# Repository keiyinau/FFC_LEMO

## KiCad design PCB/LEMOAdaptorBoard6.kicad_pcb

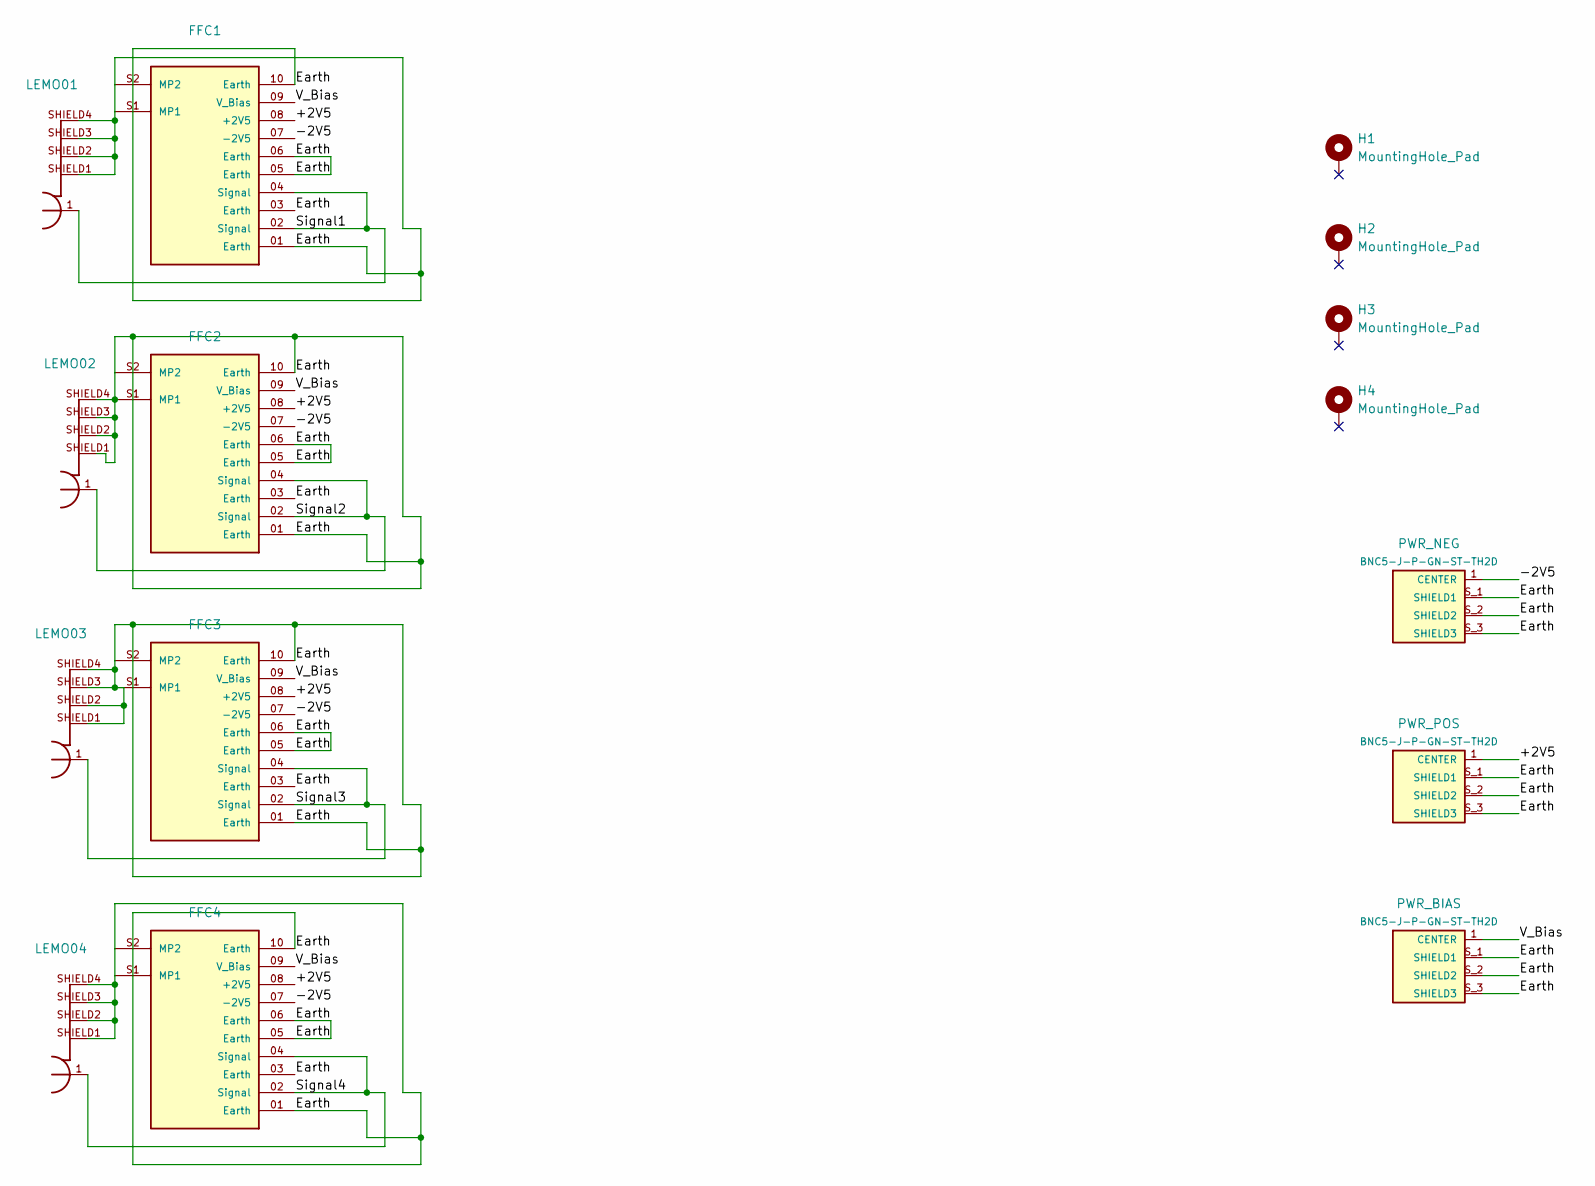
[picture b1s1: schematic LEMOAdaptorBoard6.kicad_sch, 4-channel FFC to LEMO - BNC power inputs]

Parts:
FFC1: FFC_Connector_Vertical; FFC1
FFC2: FFC_Connector_Vertical; FFC2
FFC3: FFC_Connector_Vertical; FFC3
FFC4: FFC_Connector_Vertical; FFC4
H1: MountingHole_Pad; H1
H2: MountingHole_Pad; H2
H3: MountingHole_Pad; H3
H4: MountingHole_Pad; H4
LEMO01: FPL.00.250.NTD; LEMO01
LEMO02: FPL.00.250.NTD; LEMO02
LEMO03: FPL.00.250.NTD; LEMO03
LEMO04: FPL.00.250.NTD; LEMO04
PWR_BIAS: BNC5-J-P-GN-ST-TH2D; PWR_BIAS
PWR_NEG: BNC5-J-P-GN-ST-TH2D; PWR_NEG
PWR_POS: BNC5-J-P-GN-ST-TH2D; PWR_POS

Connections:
/+2V5: FFC1.08 (+2V5), FFC2.08 (+2V5), FFC3.08 (+2V5), FFC4.08 (+2V5), PWR_POS.1 (CENTER)
/-2V5: FFC1.07 (-2V5), FFC2.07 (-2V5), FFC3.07 (-2V5), FFC4.07 (-2V5), PWR_NEG.1 (CENTER)
/Earth: FFC1.01 (Earth), FFC1.03 (Earth), FFC1.05 (Earth), FFC1.06 (Earth), FFC1.10 (Earth), FFC1.S1 (MP1), FFC1.S2 (MP2), FFC2.01 (Earth), FFC2.03 (Earth), FFC2.05 (Earth), FFC2.06 (Earth), FFC2.10 (Earth), FFC2.S1 (MP1), FFC2.S2 (MP2), FFC3.01 (Earth), FFC3.03 (Earth), FFC3.05 (Earth), FFC3.06 (Earth), FFC3.10 (Earth), FFC3.S1 (MP1), FFC3.S2 (MP2), FFC4.01 (Earth), FFC4.03 (Earth), FFC4.05 (Earth), FFC4.06 (Earth), FFC4.10 (Earth), FFC4.S1 (MP1), FFC4.S2 (MP2), LEMO01.SHIELD1, LEMO01.SHIELD2, LEMO01.SHIELD3, LEMO01.SHIELD4, LEMO02.SHIELD1, LEMO02.SHIELD2, LEMO02.SHIELD3, LEMO02.SHIELD4, LEMO03.SHIELD1, LEMO03.SHIELD2, LEMO03.SHIELD3, LEMO03.SHIELD4, LEMO04.SHIELD1, LEMO04.SHIELD2, LEMO04.SHIELD3, LEMO04.SHIELD4, PWR_BIAS.S_1 (SHIELD1), PWR_BIAS.S_2 (SHIELD2), PWR_BIAS.S_3 (SHIELD3), PWR_NEG.S_1 (SHIELD1), PWR_NEG.S_2 (SHIELD2), PWR_NEG.S_3 (SHIELD3), PWR_POS.S_1 (SHIELD1), PWR_POS.S_2 (SHIELD2), PWR_POS.S_3 (SHIELD3)
/Signal1: FFC1.02 (Signal), FFC1.04 (Signal), LEMO01.1
/Signal2: FFC2.02 (Signal), FFC2.04 (Signal), LEMO02.1
/Signal3: FFC3.02 (Signal), FFC3.04 (Signal), LEMO03.1
/Signal4: FFC4.02 (Signal), FFC4.04 (Signal), LEMO04.1
/V_Bias: FFC1.09 (V_Bias), FFC2.09 (V_Bias), FFC3.09 (V_Bias), FFC4.09 (V_Bias), PWR_BIAS.1 (CENTER)

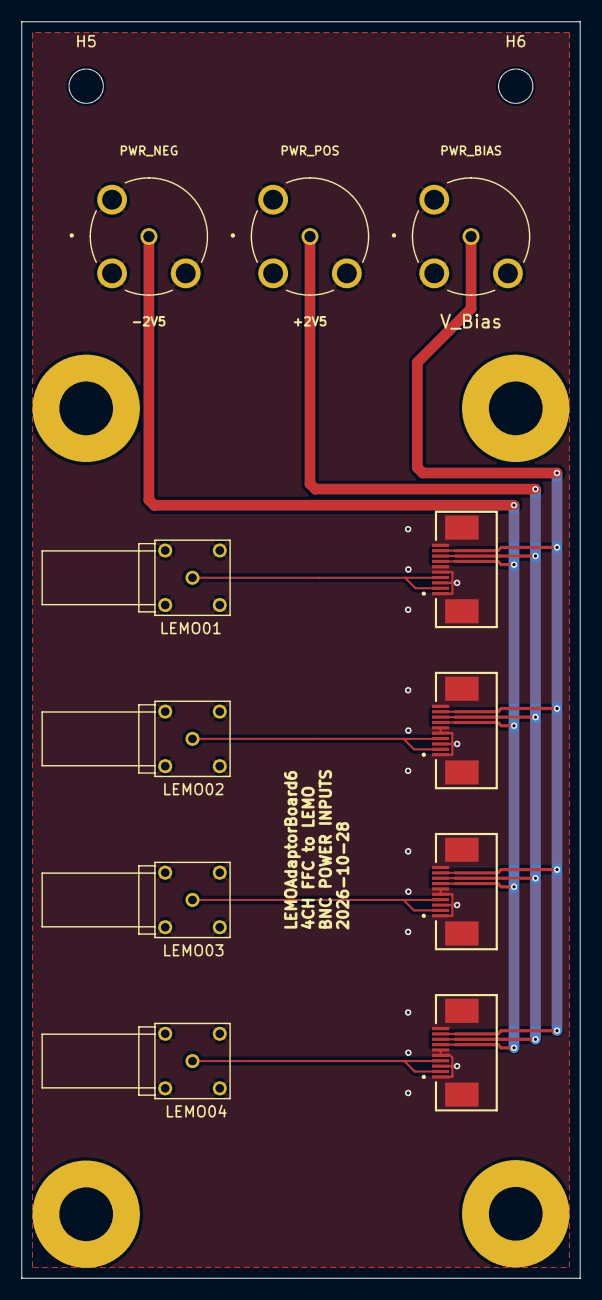
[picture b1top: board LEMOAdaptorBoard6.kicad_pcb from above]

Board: 2 copper layers, 52.0 x 117.0 mm, 17 parts (0 on the bottom side), 8 nets.

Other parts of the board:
H5, H6: MountingHole_3.2mm_M3
